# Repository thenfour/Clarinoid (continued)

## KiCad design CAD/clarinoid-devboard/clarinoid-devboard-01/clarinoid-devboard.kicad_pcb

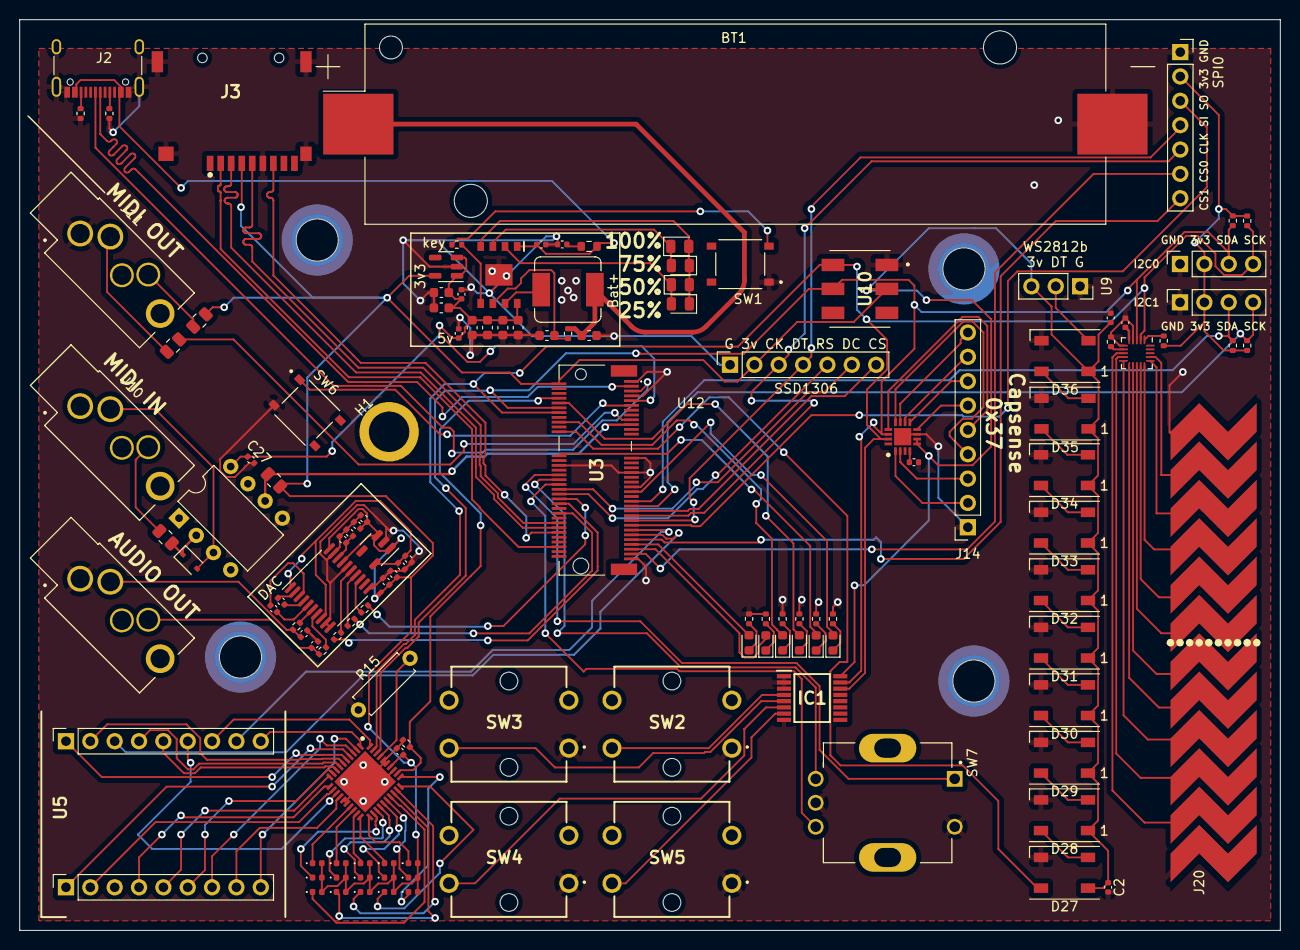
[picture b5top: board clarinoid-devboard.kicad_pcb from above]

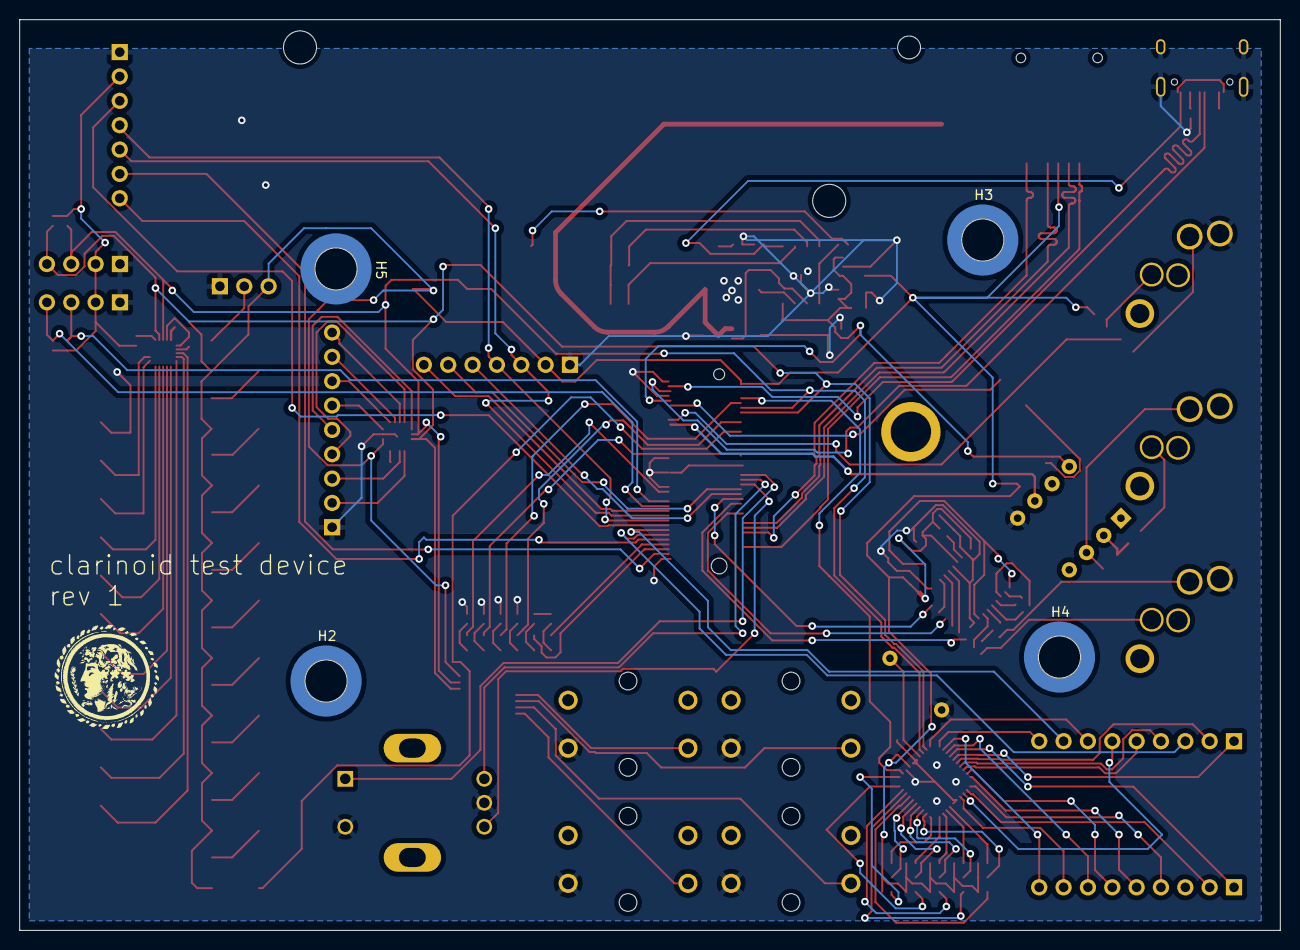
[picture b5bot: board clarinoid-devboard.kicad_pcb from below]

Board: 2 copper layers, 131.5 x 95.0 mm, 137 parts (4 on the bottom side), 144 nets.

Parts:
BT1: Battery_Cell; BatteryHolder_Keystone_1042_1x18650
C1, C2, C4, C6, C13, C14, C23, C24, C25, C27, C30: 0.1uF; C_0402_1005Metric
C3, C5, C10, C11, C15, C16, C26: 10uF; C_0402_1005Metric
C7, C8, C9, C12: 2.2uF; C_0402_1005Metric
C17, C18, C19, C20, C21, C22: 22uF; C_0603_1608Metric
C28: 0.22uF; C_0603_1608Metric
C29: 0.1uF; C_0603_1608Metric
D1: 25%; LED_0805_2012Metric
D2: 50%; LED_0805_2012Metric
D3: 75%; LED_0805_2012Metric
D4: 100%; LED_0805_2012Metric
D5, D7: blue; LED_0603_1608Metric
D6: 1N4148WS; D_SOD-323
D8, D9: green; LED_0603_1608Metric
D10, D11: red; LED_0603_1608Metric
D12, D13, D14, D15, D25: red; LED_0402_1005Metric
D16, D17, D19, D20, D21: green; LED_0402_1005Metric
D18, D22, D23, D24, D26: blue; LED_0402_1005Metric
D27, D28, D29, D30, D31, D32, D33, D34, D35, D36: WS2812B; LED_WS2812B_PLCC4_5.0x5.0mm_P3.2mm
DS1: Kingbright PDC54-Row1-pins01-09; PinSocket_1x09_P2.54mm_Vertical
DS2: Kingbright PDC54-Row2-pins10-18; PinSocket_1x09_P2.54mm_Vertical
H1: M.2 riser SMTSO2530CTJ; Sinhoo SMTSO2530CTJ
H2, H3, H4, H5: MountingHole; Wurth Elektronik Reverse SMD Spacer M3
IC1: PCA9554APW,118; SOP65P640X110-16N
IC2: Injoinic IP5306 battery charge; SOIC127P599X155-9N
IC3: IS32FL3240-QWLA3-TR; QFN50P600X600X80-41N-D
IC4: CY8CMBR3108-LQXIT; QFN50P300X300X60-17N-D
J1: AudioOut; SWITCHCRAFT_35RAPC4BV4
J2: XKB_U262-16XN-4BVC11 USB-C recept; USB_C_Receptacle_XKB_U262-16XN-4BVC11
J3: microSD SOFNG TF-15x15; SOFNG TF-15x15 (LCSC C111196)
J4: header_spi; PinSocket_1x07_P2.54mm_Vertical
J5: header_i2c; PinSocket_1x04_P2.54mm_Vertical
J6: header_i2c1; PinSocket_1x04_P2.54mm_Vertical
J10: MIDI IN; SWITCHCRAFT_35RAPC4BV4
J11: MIDI OUT; SWITCHCRAFT_35RAPC4BV4
J12: SSD1306; PinSocket_1x07_P2.54mm_Vertical
J14: touch_conn_capsense; PinSocket_1x09_P2.54mm_Vertical
J20: CapTouchSlider3; CaptouchSlider_Masked_H3x3_A1.0mm_x12
L1: 1uH; Inductor_MCS0630-1R0MN2
NT1: NetTie_2; NetTie-2_SMD_Pad0.5mm
R1, R2, R3: 22R; R_0402_1005Metric
R4, R10: 10k; R_0402_1005Metric
R5, R6, R34, R35, R36, R37, R38, R39: 470R; R_0402_1005Metric
R7, R8: 5.1k; R_0402_1005Metric
R9: 2R; R_0603_1608Metric
R11: 0.5R; R_0402_1005Metric
R12: 75k; R_0402_1005Metric
R13, R14, R40, R41: 4.7k; R_0402_1005Metric
R15: 4.7k; R_Axial_DIN0207_L6.3mm_D2.5mm_P7.62mm_Horizontal
R16: 100k; R_0402_1005Metric
R19: 220R; R_0805_2012Metric
R20, R21: 47R; R_0805_2012Metric
R22: 470R; R_0805_2012Metric
SW1, SW6: SW_Push; XKB switch jlcpcb SW_TS-1187A-B-A-B
SW2, SW3, SW4, SW5: SW_Push; B3F-4055
SW7: RotaryEncoder_Switch_ABC12; Bourns_ENC_PEC11R-4215F-S0024
U1: PCM5102A; TSSOP-20_4.4x6.5mm_P0.65mm
U2: Micromod outline; Teensy_4.0_MicroMod outline fab
U3: APCI0136-P001A Teensy_4.0_MicroMod; 21992304
U4: MPR121, 0x5A; UQFN-20_3x3mm_P0.4mm
U5: Placeholder; Kingbright PDC54 template
U7: TLV75533PDBV; SOT-23-5
U8: 6N138; DIP-8_W7.62mm
U9: WS2812; PinSocket_1x03_P2.54mm_Vertical
U10: Pressure1_0x28_I2C0; ABPMAND001PG2A3
U11: TLV75733PDBV; SOT-23-5
U12: ssd1306_graphic; SSD1306_128x64_approximate

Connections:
+3V3: C1.1, C2.1, C5.1, C6.1, C25.1, D12.2 (A), D13.2 (A), D14.2 (A), D15.2 (A), D16.2 (A), D17.2 (A), D18.2 (A), D19.2 (A), D20.2 (A), D21.2 (A), D22.2 (A), D23.2 (A), D24.2 (A), D25.2 (A), D26.2 (A), D27.1 (VDD), D28.1 (VDD), D29.1 (VDD), D30.1 (VDD), D31.1 (VDD), D32.1 (VDD), D33.1 (VDD), D34.1 (VDD), D35.1 (VDD), D36.1 (VDD), IC1.16 (VDD), IC3.34 (VCC), IC4.5 (VDDIO), IC4.6 (VDD), J3.4 (VDD_vin), J4.2, J5.2, J6.2, J12.2 (VDD), NT1.1, R4.2, R13.2, R14.2, R20.2, R22.1, R40.2, R41.2, U3.2 (3.3v), U4.20 (VDD), U9.3 (+5v), U10.2 (Vs), U11.5 (OUT)
A3v3: C3.1, C4.1, U1.1 (CPVDD), U1.8 (AVDD), U7.5 (OUT)
Batt+: BT1.1 (+), C19.1, L1.2, R11.1
D3v3: C11.2, C14.2, NT1.2, U1.17 (XSMT), U1.20 (DVDD), U7.1 (IN), U7.3 (EN)
ENC_A: SW7.A, U3.42 (41_G1)
ENC_B: SW7.B, U3.44 (42_G2)
ENC_SWITCH: SW7.1 (SWGND), U3.40 (40_G0)
GEN_LED1: D5.2 (A), U3.47 (2_PWM1)
GEN_LED2: D7.2 (A), U3.32 (3_PWM0)
GEN_LED3: D8.2 (A), U3.10 (4_D0)
GEN_LED4: D9.2 (A), U3.18 (5_D1)
GEN_LED5: D10.2 (A), U3.71 (6_G6)
GEN_LED6: D11.2 (A), U3.69 (9_G7)
GND: BT1.2 (-), C1.2, C2.2, C3.2, C4.2, C5.2, C6.2, C9.2, C10.2, C11.1, C12.2, C13.2, C14.1, C15.2, C16.2, C17.2, C18.2, C19.2, C20.2, C21.2, C22.2, C23.2, C24.2, C25.2, C26.2, C27.2, C28.2, C29.2, C30.2, D27.3 (VSS), D28.3 (VSS), D29.3 (VSS), D30.3 (VSS), D31.3 (VSS), D32.3 (VSS), D33.3 (VSS), D34.3 (VSS), D35.3 (VSS), D36.3 (VSS), IC1.1 (A0), IC1.2 (A1), IC1.3 (A2), IC1.8 (VSS), IC2.9 (PWR-GND), IC3.15 (GND_1), IC3.16 (GND_2), IC3.33 (AD), IC3.35 (GND_3), IC3.36 (GND_4), IC3.41 (EP), IC4.7 (VSS), IC4.17 (EP), J1.1 (S-GND), J2.A1 (GND), J2.A12 (GND), J2.B1 (GND), J2.B12 (GND), J2.S1 (SHIELD), J3.6 (VSS_gnd), J3.MP1 (SHIELD), J3.MP2 (SHIELD), J3.MP3 (SHIELD), J3.MP4 (SHIELD), J4.1, J5.1, J6.1, J11.1 (S-GND), J12.1 (GND), J14.1, J20.1, J20.12, R7.1, R8.1, R12.2, R15.1, R16.2, R34.2, R35.2, R36.2, R37.2, R38.2, R39.2, SW1.1, SW2.1, SW3.1, SW4.1, SW5.1, SW6.2, SW7.2 (SW), SW7.C (GND), U1.9 (AGND), U1.10 (DEMP), U1.11 (FLT), U1.16 (FMT), U1.19 (DGND), U3.1 (GND), U3.7 (GND), U3.33 (GND), U3.36 (GND), U3.39 (GND), U3.45 (GND), U3.75 (GND), U4.4 (ADDR), U4.6 (VSS), U7.2 (GND), U8.5 (GND), U9.1 (gnd), U10.1 (GND), U11.2 (GND)
I2C1_SCL: J6.4, R14.1, U3.53 (24_SCL1_A10)
I2C1_SDA: J6.3, R13.1, U3.51 (25_SDA1_A11)
I2C_SCL: IC1.14 (SCL), IC3.39 (SCL), IC4.15 (I2C_SCL), J5.4, R41.1, U3.14 (19_SCL_A5), U4.2 (SCL), U10.6 (SCL)
I2C_SDA: IC1.15 (SDA), IC3.38 (SDA), IC4.14 (I2C_SDA), J5.3, R40.1, U3.12 (18_SDA_A4), U4.3 (SDA), U10.5 (SDA)
I2S_BCK: R3.1, U3.50 (21_BCLK_A7)
I2S_DIN: R2.1, U3.56 (7_AUD_OUT)
I2S_LRCK: R1.1, U3.52 (20_LRCLK_A6)
unnamed: C7.1, U1.2 (CAPP)
unnamed: C7.2, U1.4 (CAPM)
unnamed: C8.1, U1.5 (VNEG)
unnamed: C8.2, U1.3 (CPGND)
unnamed: C9.1, J1.2 (Tip), R5.2
unnamed: C10.1, C13.1, U1.18 (LDOO)
unnamed: C12.1, J1.4 (Ring), R6.2
unnamed: C15.1, R9.2
unnamed: C18.1, IC2.6 (BAT), R11.2
unnamed: C24.1, U4.5 (VREG)
unnamed: C30.1, IC4.4 (VCC)
unnamed: D1.1 (K), D2.2 (A), D3.1 (K), D4.2 (A), IC2.4 (LED3)
unnamed: D1.2 (A), D2.1 (K), IC2.2 (LED1)
unnamed: D3.2 (A), D4.1 (K), IC2.3 (LED2)
unnamed: D5.1 (K), R34.1
unnamed: D6.1 (K), R19.2, U8.2 (C1)
unnamed: D6.2 (A), J10.2 (Tip), U8.3 (C2)
unnamed: D7.1 (K), R35.1
unnamed: D8.1 (K), R36.1
unnamed: D9.1 (K), R37.1
unnamed: D10.1 (K), R38.1
unnamed: D11.1 (K), R39.1
unnamed: D12.1 (K), IC3.20 (OUT19)
unnamed: D14.1 (K), IC3.18 (OUT17)
unnamed: D15.1 (K), IC3.17 (OUT16)
unnamed: D27.2 (DOUT), D28.4 (DIN)
unnamed: D28.2 (DOUT), D29.4 (DIN)
unnamed: D29.2 (DOUT), D30.4 (DIN)
unnamed: D30.2 (DOUT), D31.4 (DIN)
unnamed: D31.2 (DOUT), D32.4 (DIN)
unnamed: D32.2 (DOUT), D33.4 (DIN)
unnamed: D33.2 (DOUT), D34.4 (DIN)
unnamed: D34.2 (DOUT), D35.4 (DIN)
unnamed: D35.2 (DOUT), D36.4 (DIN)
unnamed: IC1.4 (IO0), SW2.2
unnamed: IC1.5 (IO1), SW3.2
unnamed: IC1.6 (IO2), SW4.2
unnamed: IC1.7 (IO3), SW5.2
unnamed: IC2.5 (KEY), R10.1
unnamed: IC2.7 (SW-inductor), L1.1
unnamed: DS2.9 (10_ANODE_B), IC3.1 (OUT2)
unnamed: DS1.9 (ANODE_C), IC3.2 (OUT3)
unnamed: DS1.7 (ANODE_D), IC3.3 (OUT4)
unnamed: DS1.1 (ANODE_E), IC3.4 (OUT5)
unnamed: DS2.1 (18_ANODE_F), IC3.5 (OUT6)
unnamed: DS2.2 (17_ANODE_G), IC3.6 (OUT7)
unnamed: DS2.4 (15_ANODE_H), IC3.7 (OUT8)
unnamed: DS2.5 (14_ANODE_J), IC3.8 (OUT9)
unnamed: DS1.6 (ANODE_K), IC3.9 (OUT10)
unnamed: DS1.5 (ANODE_L), IC3.10 (OUT11)
unnamed: DS1.4 (ANODE_M), IC3.11 (OUT12)
unnamed: DS1.2 (ANODE_N), IC3.12 (OUT13)
unnamed: DS2.6 (13_ANODE_P), IC3.13 (OUT14)
unnamed: DS1.8 (ANODE_DP1/DP2), IC3.14 (OUT15)
unnamed: D13.1 (K), IC3.19 (OUT18)
unnamed: D25.1 (K), IC3.21 (OUT20)
unnamed: D16.1 (K), IC3.22 (OUT21)
unnamed: D19.1 (K), IC3.23 (OUT22)
unnamed: D17.1 (K), IC3.24 (OUT23)
unnamed: D20.1 (K), IC3.25 (OUT24)
unnamed: D21.1 (K), IC3.26 (OUT25)
unnamed: D22.1 (K), IC3.27 (OUT26)
unnamed: D23.1 (K), IC3.28 (OUT27)
unnamed: D18.1 (K), IC3.29 (OUT28)
unnamed: D24.1 (K), IC3.30 (OUT29)
unnamed: D26.1 (K), IC3.31 (OUT30)
unnamed: IC3.37 (ISET), R15.2
unnamed: DS2.7 (12_ANODE_A), IC3.40 (OUT1)
unnamed: IC4.1 (CS0/PS0), J14.2
unnamed: IC4.2 (CS1/PS1), J14.3
unnamed: IC4.8 (CS4/GPO0), J14.6
unnamed: IC4.9 (CS5/GPO1), J14.7
unnamed: IC4.10 (CS6/GPO2), J14.8
unnamed: IC4.11 (CS7/GPO3/SH), J14.9
unnamed: IC4.12 (CS2/GUARD), J14.4
unnamed: IC4.13 (CS3), J14.5
unnamed: J2.A5 (CC), R8.2
unnamed: J2.B5 (VCONN), R7.2
unnamed: J10.4 (Ring), R19.1
unnamed: J11.2 (Tip), R21.1
unnamed: J11.4 (Ring), R20.1
unnamed: J20.2, U4.8 (ELE0)
unnamed: J20.3, U4.9 (ELE1)
unnamed: J20.4, U4.10 (ELE2)
unnamed: J20.5, U4.11 (ELE3)
unnamed: J20.6, U4.12 (LED0/ELE4)
unnamed: J20.7, U4.13 (LED1/ELE5)
unnamed: J20.8, U4.14 (LED2/ELE6)
unnamed: J20.9, U4.15 (LED3/ELE7)
unnamed: J20.10, U4.16 (LED4/ELE8)
unnamed: J20.11, U4.17 (LED5/ELE9)
unnamed: R1.2, U1.15 (LRCK)
unnamed: R2.2, U1.14 (DIN)
unnamed: R3.2, U1.13 (BCK)
unnamed: R4.1, U4.1 (~IRQ)
unnamed: R5.1, U1.6 (OUTL)
unnamed: R6.1, U1.7 (OUTR)
unnamed: R10.2, SW1.2
unnamed: R12.1, U4.7 (REXT)
unnamed: SW6.1, U3.11 (PROGRAM)
OLED_CS: J12.7 (CS), U3.55 (10_SPI_CS)
OLED_DC: J12.6 (DC), U3.46 (43_G3)
OLED_RES: J12.5 (RES), U3.48 (44_G4)
SDIO_CLOCK: J3.5 (CLK), U3.60 (36_SDIO_CLK)
SDIO_CS: J3.2 (SS_CS_CD/DAT3^2), U3.70 (39_SDIO_DATA3)
SDIO_MISO: J3.7 (MISO_DAT0), U3.64 (35_SDIO_DATA0)
SDIO_MOSI: J3.3 (MOSI_CMD), U3.62 (37_SDIO_CMD)
SPI0_MISO: J4.3, U3.61 (12_SPI_SDI)
SPI0_MOSI: J4.4, J12.4 (SDA), U3.59 (11_SPI_SDO)
SPI0_SCK: J4.5, J12.3 (SCK), U3.57 (13_SPI_SCK)
SPI0_generic0_cs: J4.6, U3.73 (45_G5)
SPI0_generic1_cs: J4.7, U3.67 (26_G8_A12)
Supply+5v: C17.1, C20.1, C21.1, C22.1, C23.1, C26.1, C27.1, C28.1, C29.1, IC2.8 (VOUT), U3.9 (VUSB), U8.8 (VCC), U11.1 (IN), U11.3 (EN)
T00 MIDI IN: R22.2, U3.19 (0_RX1), U8.6 (VO2)
T01=MIDI OUT: R21.2, U3.17 (1_TX1)
USB data in +: J2.A6 (D+), U3.3 (D+)
USB data in -: J2.A7 (D-), U3.5 (D-)
USB_Vin5v: C16.1, IC2.1 (VIN), J2.A4 (VBUS), J2.A9 (VBUS), J2.B4 (VBUS), J2.B9 (VBUS), R9.1
WS2812_DATA: D27.4 (DIN), U3.22 (17_TX2_A3)
WS2812_DATA2: D36.2 (DOUT), U9.2 (Data)
enable_led_driver: IC3.32 (SDB), R16.1, U3.8 (27_G11_A13)
kingbright_dig0: DS2.3 (16_COMMON_CATHODE_DIG_1), U3.65 (32_G9_ADCD-)
kingbright_dig1: DS2.8 (11_COMMON_CATHODE_DIG_2), U3.63 (33_G10_ADCD+)

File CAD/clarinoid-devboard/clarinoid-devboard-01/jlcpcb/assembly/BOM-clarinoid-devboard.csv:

Comment,Designator,Footprint,LCSC
Battery_Cell,"BT1,H2,H3,H4,H5,J1,J10,J11,J20,NT1,SW7,U10",BatteryHolder_Keystone_1042_1x18650,-
PCM5102A,U1,TSSOP-20_4.4x6.5mm_P0.65mm,C107671
microSD SOFNG TF-15x15,J3,SOFNG TF-15x15 (LCSC C111196),C111196
2.2uF,"C12,C7,C8,C9",C_0402_1005Metric,C12530
WS2812,U9,PinSocket_1x03_P2.54mm_Vertical,C146243
0.1uF,C29,C_0603_1608Metric,C14663
0.1uF,"C13,C14,C23,C24,C25,C27,C30,C4,C6",C_0402_1005Metric,C1525
10uF,"C10,C11,C15,C16,C26,C3,C5",C_0402_1005Metric,C15525
220R,R19,R_0805_2012Metric,C17557
470R,R22,R_0805_2012Metric,C17710
47R,"R20,R21",R_0805_2012Metric,C17714
Injoinic IP5306 battery charge,IC2,SOIC127P599X155-9N,C181692
0.22uF,C28,C_0603_1608Metric,C21120
1N4148WS,D6,D_SOD-323,C2128
2R,R9,R_0603_1608Metric,C22977
22R,"R1,R2,R3",R_0402_1005Metric,C25092
470R,"R34,R35,R36,R37,R38,R39,R5,R6",R_0402_1005Metric,C25117
10k,"R10,R13,R14,R17,R18,R4,R40,R41,R43,R44",R_0402_1005Metric,C25744
75k,R12,R_0402_1005Metric,C25798
5.1k,"R7,R8",R_0402_1005Metric,C25905
25%,"D1,D2,D3,D4",LED_0805_2012Metric,C264424
header_i2c,J5,PinSocket_1x04_P2.54mm_Vertical,C2718488
M.2 riser SMTSO2530CTJ ,H1,Sinhoo SMTSO2530CTJ,C2915631
SW_Push,"SW1,SW6",XKB switch jlcpcb SW_TS-1187A-B-A-B,C318884
XKB_U262-16XN-4BVC11 USB-C recept,J2,USB_C_Receptacle_XKB_U262-16XN-4BVC11,C319148
SSD1306,J12,PinSocket_1x07_P2.54mm_Vertical,C358721
1uH,L1,Inductor_MCS0630-1R0MN2,C385251
touch_conn_capsense,J14,PinSocket_1x09_P2.54mm_Vertical,C39576
TLV75533PDBV,U7,SOT-23-5,C404027
CY8CMBR3108-LQXIT,IC4,QFN50P300X300X60-17N-D,C462528
TLV75733PDBV,U11,SOT-23-5,C485517
6N138,U8,DIP-8_W7.62mm,C571211
22uF,"C17,C18,C19,C20,C21,C22",C_0603_1608Metric,C59461
blue,"D5,D7",LED_0603_1608Metric,C72041
green,"D8,D9",LED_0603_1608Metric,C72043
red,"D10,D11",LED_0603_1608Metric,C72044
APCI0136-P001A Teensy_4.0_MicroMod,U3,21992304,C841670
SW_Push,"SW2,SW3,SW4,SW5",B3F-4055,C84931
"PCA9554APW,118",IC1,SOP65P640X110-16N,C86803
0.5R,R11,R_0402_1005Metric,C880273
"MPR121, 0x5A",U4,UQFN-20_3x3mm_P0.4mm,C91322
